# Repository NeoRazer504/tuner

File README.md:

# Tuner
This is a chromatic instrument tuner I made for myself because I'm a band nerd and I need a better tuner so instead of buying one, I thought it would be better to make one :). (This is my first custom project so hope it works🙏).
## Features
- Powered by a Xiao nRF52840
- Built in microphone and a jack so you can choose to use a external mic instead
- 2.42" OLED
- 3 LEDs to indicate if you're flat, sharp, or in tune
- 2 buttons to adjust hertz
- 500 mAh battery
## Gallery

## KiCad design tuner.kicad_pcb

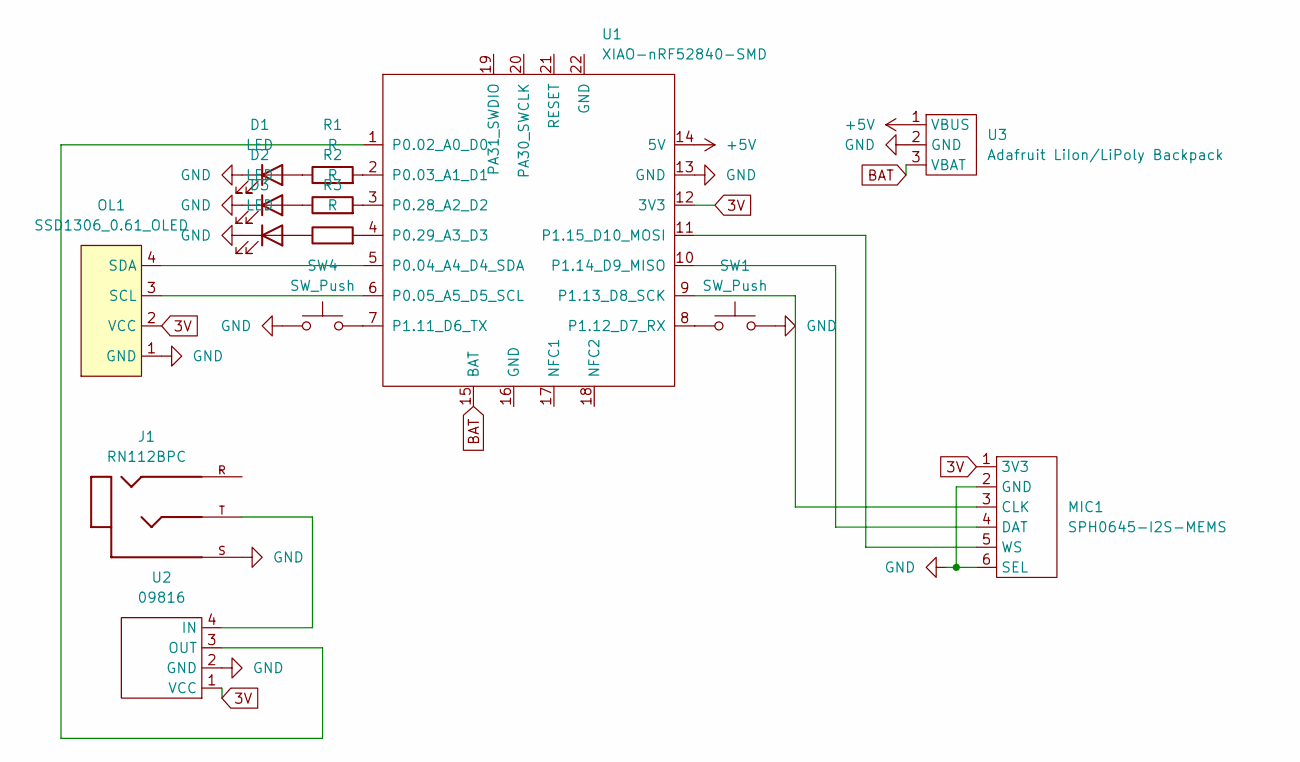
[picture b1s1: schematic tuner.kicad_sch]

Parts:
D1, D2, D3: LED; LED_D5.0mm
J1: RN112BPC; SWITCHCRAFT_RN112BPC; PARTREV E
MIC1: SPH0645-I2S-MEMS; Adafruit-SPH0645-I2S-MEMS-Mic
OL1: SSD1306_0.61_OLED; 2.42_ oled
R1, R2, R3: R; R_Axial_DIN0207_L6.3mm_D2.5mm_P7.62mm_Horizontal
SW1, SW4: SW_Push; SW_PUSH_6mm
U1: XIAO-nRF52840-SMD; XIAO-nRF52840-SMD-V2
U2: 09816
U3: Adafruit LiIon/LiPoly Backpack; battery backpack

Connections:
3V: MIC1.1 (3V3), OL1.2 (VCC), U1.12 (3V3), U2.1 (VCC)
+5V: U1.14 (5V), U3.1 (VBUS)
BAT: U1.15 (BAT), U3.3 (VBAT)
GND: D1.1 (K), D2.1 (K), D3.1 (K), J1.S, MIC1.2 (GND), MIC1.6 (SEL), OL1.1 (GND), SW1.2, SW4.1, U1.13 (GND), U2.2 (GND), U3.2 (GND)
unnamed: D1.2 (A), R1.1
unnamed: D2.2 (A), R2.1
unnamed: D3.2 (A), R3.1
unnamed: MIC1.3 (CLK), U1.9 (P1.13_D8_SCK)
unnamed: MIC1.4 (DAT), U1.10 (P1.14_D9_MISO)
unnamed: MIC1.5 (WS), U1.11 (P1.15_D10_MOSI)
unnamed: OL1.3 (SCL), U1.6 (P0.05_A5_D5_SCL)
unnamed: OL1.4 (SDA), U1.5 (P0.04_A4_D4_SDA)
unnamed: U1.1 (P0.02_A0_D0), U2.3 (OUT)
unnamed: R1.2, U1.2 (P0.03_A1_D1)
unnamed: R2.2, U1.3 (P0.28_A2_D2)
unnamed: R3.2, U1.4 (P0.29_A3_D3)
unnamed: SW4.2, U1.7 (P1.11_D6_TX)
unnamed: SW1.1, U1.8 (P1.12_D7_RX)
unnamed: J1.T, U2.4 (IN)

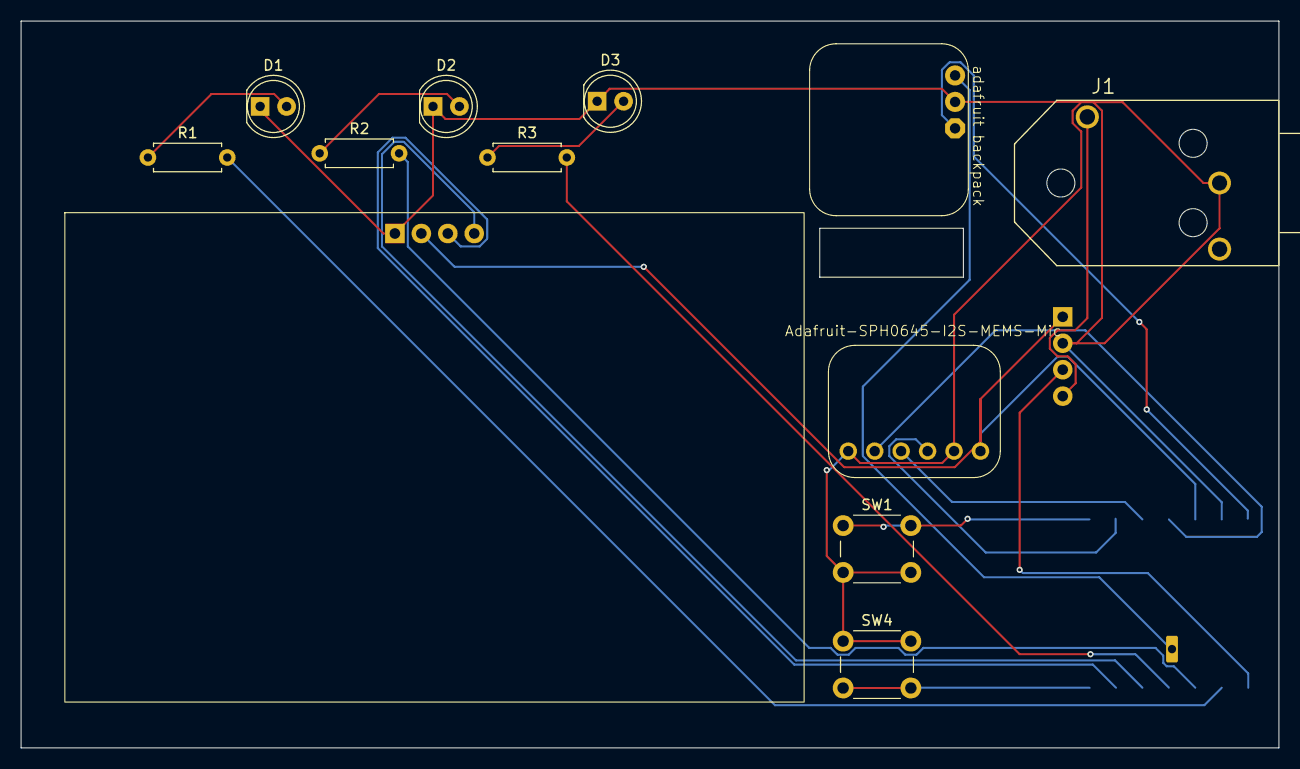
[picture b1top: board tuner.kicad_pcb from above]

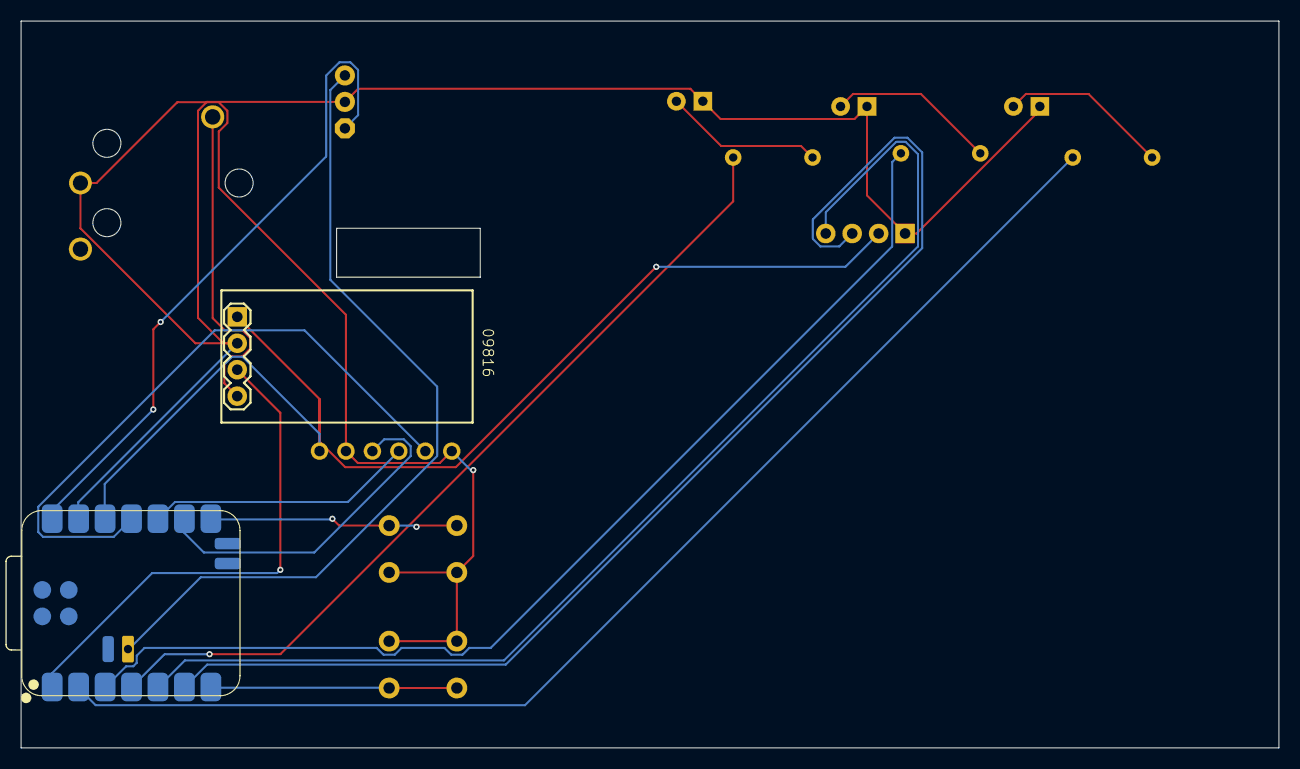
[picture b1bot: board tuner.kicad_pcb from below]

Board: 2 copper layers, 120.8 x 69.8 mm, 14 parts (2 on the bottom side), 19 nets.

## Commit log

2025-12-27 Rename tuner.zip to pcb/tuner.zip
2025-12-27 Rename tuner.kicad_pro to pcb/tuner.kicad_pro
2025-12-27 Rename tuner.step to pcb/tuner.step
2025-12-27 Create a
2025-12-27 Rename tuner.ino to firmware/tuner.ino
2025-12-28 Rename tuner 1.step to assembly.step
2025-12-28 Add README for Tuner project
    Added a README file detailing the Tuner project, its features, and a gallery of images.
2025-12-28 Add 500 mAh battery specification
    Add battery specification to product features
2025-12-28 Add BOM.csv with XIAO nRF52840 details
2025-12-28 Add components and costs to BOM.csv
2025-12-28 Correct formatting of 1/4 inch Jack description
2025-12-28 Update README with project background information
    Added a note about this being the first custom project.
2025-12-28 Revise README description for clarity
    Updated project description for clarity and removed 'non guided' reference.
2025-12-28 Change URL for Xiao nRF52840 in BOM.csv
    Updated the URL for the Xiao nRF52840 microcontroller.
2025-12-28 Revise BOM with new component details and costs
    Updated BOM.csv with new URLs and costs for components.
2026-01-18 Update BOM.csv with new PCB cost and total cost
2026-01-18 Update gallery with additional images
    Added two new images to the gallery section.
